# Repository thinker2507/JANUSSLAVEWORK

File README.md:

F20240824H
TASK 1 

This flight software is designed for a CanSat using a Quectel L89HA GNSS module. The software performs the following functions:

* Reads NMEA \$GNGGA sentences from the GNSS module.
* Parses UTC time, latitude, longitude, and MSL altitude.
* Implements a flight state machine for the states: IDLE, ASCENT, APOGEE, DESCENT, PAYLOAD DEPLOYED, and LANDED.
* Prints all relevant data to the Serial Monitor for real-time monitoring.

Hardware Setup

* Arduino board (Uno, Nano, or MEGA)
* Quectel L89HA GNSS Module

Connections

* GNSS Module TX/RX to Arduino TX0/RX0 (hardware UART)
* Arduino USB connection to PC for Serial Monitor output

GNSS Configuration

* Baud rate: 9600 bps (default)
* NMEA output: only \$GNGGA enabled
* Quectel commands to configure the module:
  Serial.println("\$PQTXT,W,0");       // Disable all NMEA sentences
  Serial.println("\$PQTXT,W,1,GNGGA"); // Enable only GNGGA

Flight State Machine

* IDLE: CanSat is stationary on the ground.
* ASCENT: CanSat is ascending.
* APOGEE: CanSat has reached its peak altitude.
* DESCENT: CanSat is descending without the payload deployed.
* PAYLOAD DEPLOYED: CanSat is descending after the payload has been deployed at 75% of peak altitude.
* LANDED: CanSat has landed on the ground.

Software Logic

* Previous altitude is compared with current altitude to determine ascent or descent.
* Peak altitude is recorded when ascent stops.
* Payload deployment is triggered at 75% of peak altitude.
* All flight data (time, latitude, longitude, altitude, state) is printed to the Serial Monitor.

Serial Monitor Output
The output format for each reading is:
Time: HH\:MM\:SS | Lat: <latitude> | Lon: <longitude> | Alt: <altitude> m | State: \<flight\_state>

Notes

* The software relies on a valid GNSS fix for accurate altitude and position readings.
* Only \$GNGGA sentences are parsed to reduce UART traffic and simplify processing.
* Adjust the payload deployment logic or thresholds according to your mission requirements.

TASK 2

Defines two data trace objects for Plotly plots:

data2D: stores altitude against UTC time seconds (x,y arrays).

data3D: stores latitude, longitude, and altitude arrays for 3D scatter plot.

Initializes two Plotly plots with titles and axis labels on page load.

Splits the incoming NMEA line by commas.

Performs a relaxed check to allow partial sentences (minimum 6 fields for lat/lon).

Parses UTC time, latitude, longitude, and altitude from known standard indices.

Uses conversion functions to convert lat/lon formats and UTC time.

Returns an object with numeric utcSeconds, lat, lon, alt and raw UTC string.

Returns null if critical data missing or invalid.

Parses $GNGGA sentences, extracts coordinates and timing.

Plots live altitude (vs UTC time) and 3D geographic path.

TASK 3

Had to switch operating systems only have a file where components are rearranged no connections .
So could not complete task :=(

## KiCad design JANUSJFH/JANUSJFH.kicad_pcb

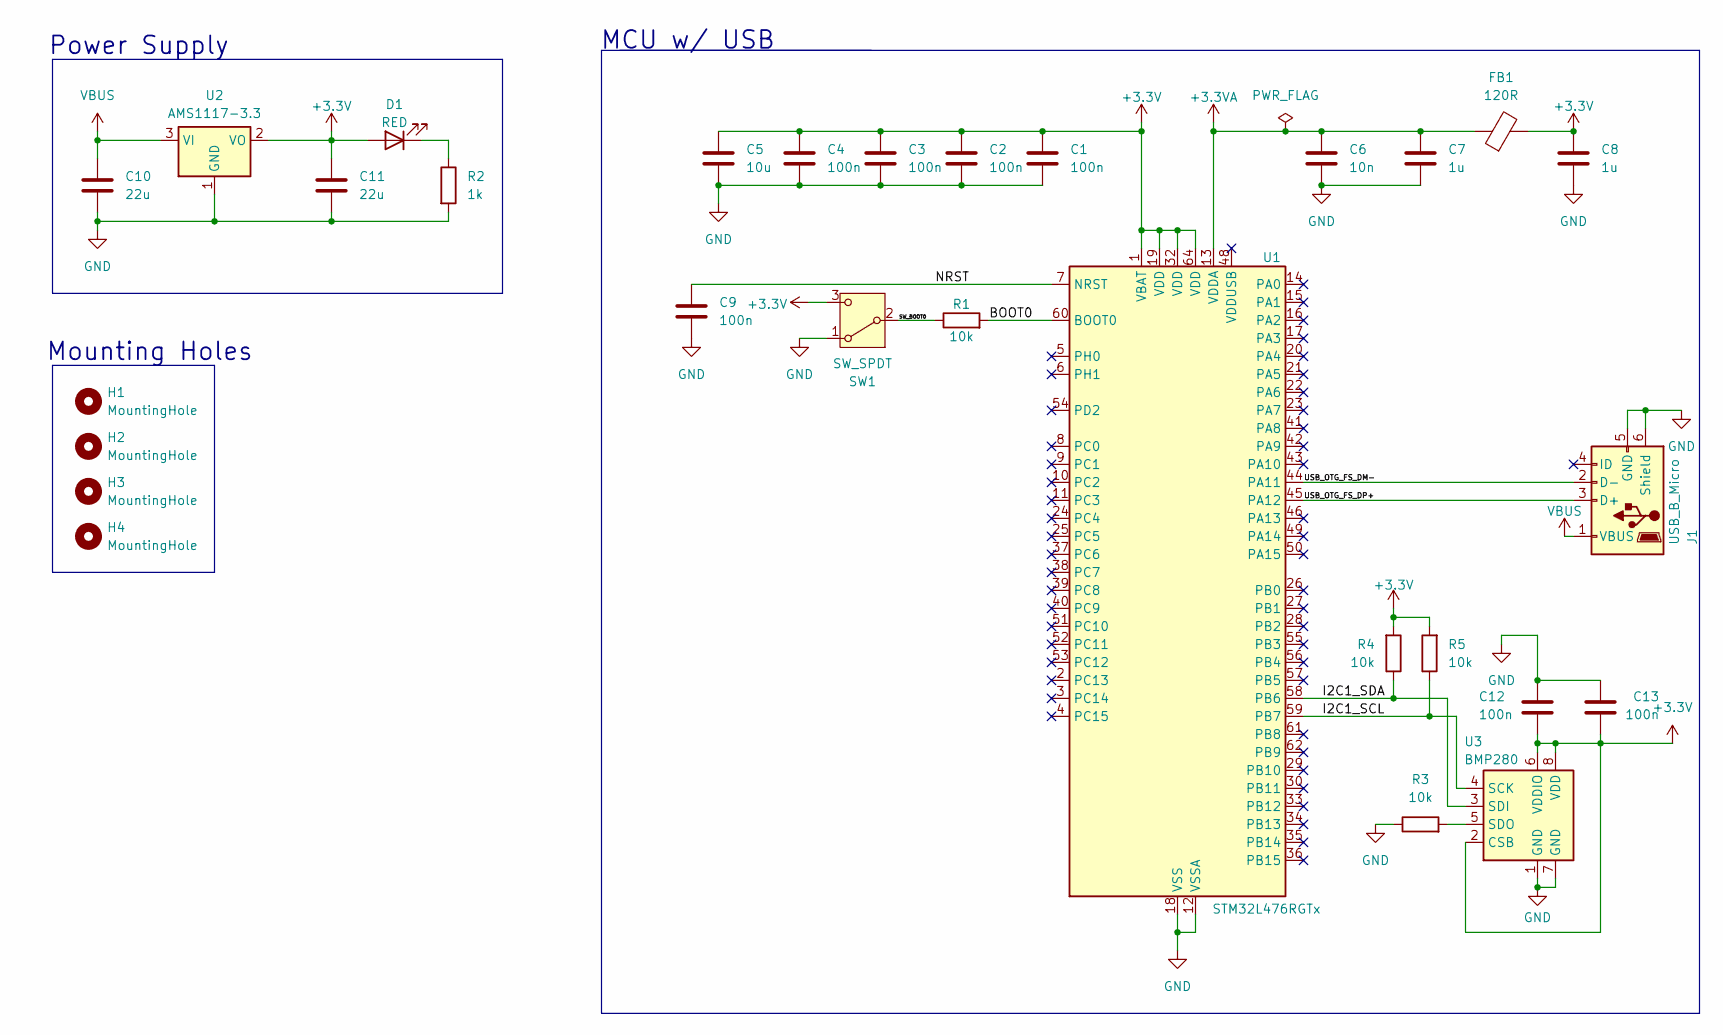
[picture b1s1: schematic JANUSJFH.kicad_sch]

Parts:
C1, C2, C3, C4, C9, C12, C13: 100n; C_0402_1005Metric
C5: 10u; C_0603_1608Metric
C6: 10n; C_0402_1005Metric
C7, C8: 1u; C_0402_1005Metric
C10, C11: 22u; C_0805_2012Metric
D1: RED; LED_0603_1608Metric
FB1: 120R; L_0603_1608Metric
H1, H2, H3, H4: MountingHole; MountingHole_2.2mm_M2
J1: USB_B_Micro; USB_Micro-B_Wuerth_629105150521
R1, R3, R4, R5: 10k; R_0402_1005Metric
R2: 1k; R_0402_1005Metric
SW1: SW_SPDT; SW_SPDT_PCM12
U1: STM32L476RGTx; LQFP-64_10x10mm_P0.5mm
U2: AMS1117-3.3; SOT-223-3_TabPin2
U3: BMP280; Bosch_LGA-8_2x2.5mm_P0.65mm_ClockwisePinNumbering

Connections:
+3.3V: C1.1, C2.1, C3.1, C4.1, C5.1, C8.1, C11.1, C12.2, C13.2, D1.2 (A), FB1.2, R4.2, R5.2, SW1.3 (C), U1.1 (VBAT), U1.19 (VDD), U1.32 (VDD), U1.64 (VDD), U2.2 (VO), U3.2 (CSB), U3.6 (VDDIO), U3.8 (VDD)
+3.3VA: C6.1, C7.1, FB1.1, U1.13 (VDDA)
/BOOT0: R1.2, U1.60 (BOOT0)
/I2C1_SCL: R5.1, U1.59 (PB7), U3.4 (SCK)
/I2C1_SDA: R4.1, U1.58 (PB6), U3.3 (SDI)
/NRST: C9.1, U1.7 (NRST)
/SW_BOOT0: R1.1, SW1.2 (B)
/USB_OTG_FS_DM-: J1.2 (D-), U1.44 (PA11)
/USB_OTG_FS_DP+: J1.3 (D+), U1.45 (PA12)
GND: C1.2, C2.2, C3.2, C4.2, C5.2, C6.2, C7.2, C8.2, C9.2, C10.2, C11.2, C12.1, C13.1, J1.5 (GND), J1.6 (Shield), R2.2, R3.1, SW1.1 (A), U1.12 (VSSA), U1.18 (VSS), U1.31 (VSS), U1.47 (VSS), U1.63 (VSS), U2.1 (GND), U3.1 (GND), U3.7 (GND)
unnamed: D1.1 (K), R2.1
unnamed: R3.2, U3.5 (SDO)
VBUS: C10.1, J1.1 (VBUS), U2.3 (VI)

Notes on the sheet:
Power Supply
MCU w/ USB
Mounting Holes

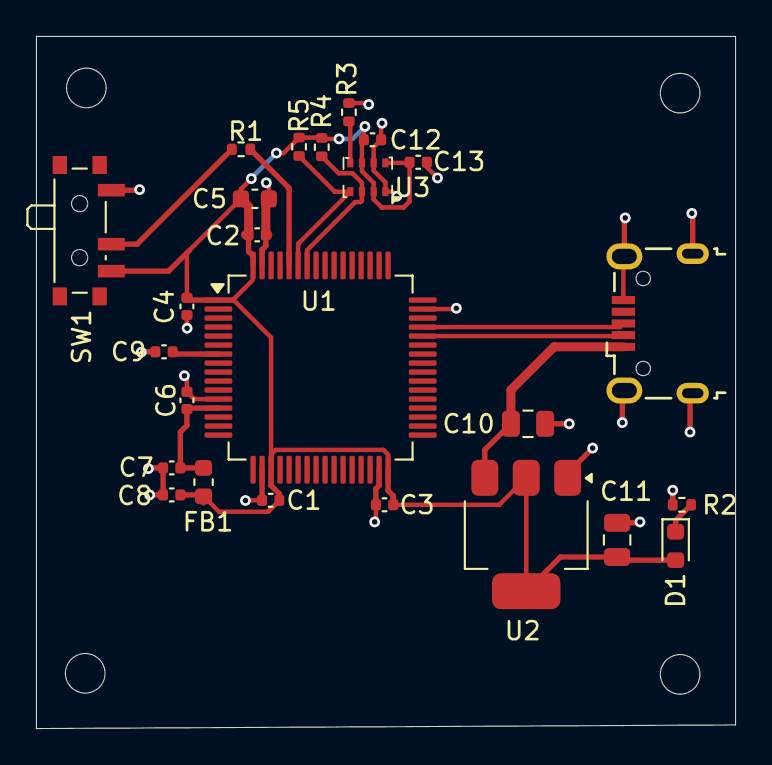
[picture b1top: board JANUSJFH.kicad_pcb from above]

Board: 2 copper layers, 38.8 x 38.5 mm, 29 parts (0 on the bottom side), 13 nets.
